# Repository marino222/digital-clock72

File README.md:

# Digital Kinetic Art Clock 

This project is the digital successor to my [ClockClock24 Project](https://github.com/marino222/clockclock24-replica), a replica of the kinetic art piece by [Humans Since 1982](https://www.humanssince1982.com/en-int). The original features physical clock hands driven by stepper motors, which brings challenges around power supply and makes scaling difficult.

This version replaces the clock hands with round LCD displays, which opens up new possibilities beyond just showing the time: animations, a snake game across all displays, or custom widgets.

---

## Table of contents

- [Vision](#vision)
- [Key decisions](#key-decisions)
- [How it works](#how-it-works)
- [Repository layout & component status](#repository-layout--component-status)
- [Roadmap](#roadmap)
- [Open questions](#open-questions)

---

## 🌅 Vision

The goal is to build a wall mounted array of round LCD displays that act together as one big synchronized screen. Each display sits in its own spot in a grid, similar to the clocks in the predecessor, but instead of physical hands every spot now has its own small screen.

At first, the array will simply show the time. But since every spot is now a real screen and not just a pair of clock hands, I plan to add more features over time. This includes smooth animations where the hands ease in and out instead of jumping, geometric patterns that move across the whole grid, a snake game that can be played across all displays at once, and small widgets like weather or notifications.

One central computer (likely a Raspberry Pi) will control the whole array and decide what should be shown. It sends this information to every display, and each display takes care of showing its own part of the picture.

---

## 🧩 Concept 

| Aspect | Choice | Why |
|---|---|---|
| Architecture | Master for calulation / Slave for rendering | Real time pixel drawing and global logic need different hardware |
| Master | Raspberry Pi 3, headless Linux broadcasts state at 60 Hz | Global logic and the web UI run better on a Pi than on a microcontroller |
| Node (Slave) | 1× bare RP2040 + 1× GC9A01 round LCD, on a small custom PCB | One identical board, JLCPCB assembled, just replicated |
| Bus | RS485, daisy chained node to node | Carries tiny state packets instead of full frames, so it scales cleanly |
| Applications | Time, animated patterns, array wide games (Snake) | All just different states broadcast by the master |

---

## ⚙️ How it works

To make the vision above work, the project splits the thinking and the drawing onto different controllers. One controller calculates the global image/animation and broadcasts these to the nodes. Each node controller then renders its individual pixels and displays them.

```
        ┌───────────────────────────────────────────────┐
        │  MASTER (Raspberry Pi 3)                      │
        │  • Headless Linux, C#                         │
        │  • Time sync, global vector math, game logic  │
        │  • Web UI for control/config                  │ 
        └───────────────────────┬───────────────────────┘
                                │  RS485 bus (broadcast)
                                │  tiny state packets @ 60 FPS
        ┌───────────┬───────────┼───────────┬───────────┐
        ▼           ▼           ▼           ▼           ▼
     ┌──────┐    ┌──────┐    ┌──────┐    ┌──────┐    ┌──────┐
     │ NODE │    │ NODE │    │ NODE │    │ NODE │    │ NODE │  
     │RP2040│    │  +   │    │  +   │    │  +   │    │  +   │
     │GC9A01│    │ LCD  │    │ LCD  │    │ LCD  │    │ LCD  │
     └──────┘    └──────┘    └──────┘    └──────┘    └──────┘
   Each node renders its own pixels locally from the shared global state.
```

### The master and the slave nodes

One computer, the master controller, runs the whole logic. It keeps track of time, decides what the array should be displaying, and runs a simple web page so it can be controlled. Every screen has its own slave controller, together they make up a node. Each node holds the picture for its own screen and draws it fast enough to keep up with all the others. It also knows its own position in the grid, so it only draws its own little piece of the bigger picture. The work is split this way because one controller can think for the whole array, but it cannot draw fast enough on dozens of screens by itself. And a tiny slave controller is fast enough to draw one screen, but it is too small to run all the planning logic. Splitting the work lets both sides do what they are good at. There is also a hard numeric reason the nodes have to render locally. One screen is 240×240 pixels at 16-bit color (RGB565), so one full frame is 240 × 240 × 2 bytes ≈ **112.5 KiB**. The RP2040 on each node has 264 KiB of SRAM, so it comfortably fits a double buffer for its *own* screen (≈225 KiB) with room to spare.

Read more about the master controller in [`master/README.md`](master/README.md), about the nodes in [`slave/README.md`](slave/README.md), and about the
hardware behind them in [`pcb/README.md`](pcb/README.md).

### How the data is sent to the nodes

Here is the idea that makes the whole array possible. The master does not send a full picture to every screen, sixty times a second. That would be far too much data. Instead, it sends a tiny instruction, something like "the hand should now point at 45 degrees" or "the snake is now at position 12, 2." Every node controller receives the exact same tiny instruction at the exact same moment, and draws its own piece of the picture from it. Streaming one full frame to one screen at 60 FPS is 112.5 KiB × 60 ≈ **6.6 MB/s**, for a single screen alone. For 9 nodes that is already ≈ 60 MB/s, at the full 72-node array it is ≈ 475 MB/s. A wired RS485 bus, the kind of connection this project uses, realistically carries somewhere in the low single-digit Mbit/s over a long daisy chain, several hundred times too little. A state instruction, on the other hand, is a handful of bytes sent once, at 60 Hz, no matter how many screens are listening. That gap is the entire reason the master only ever sends instructions, never pixels. This has three nice side effects. It needs very little data, since an instruction is just a handful of bytes instead of a full image. It keeps everything in sync automatically, since every screen hears the same instruction at the same time. And it scales easily, since adding more screens does not change how much data the brain has to send.

To reliably send state instruction a Data Protocol needs to be defined. Read more about this in [`master/README.md`](master/README.md) and [`slave/README.md`](slave/README.md).

### What actually will be displayed

This instruction can describe anything, which is what makes the project exciting. So far the plan includes:

- **Time:** the original purpose, digits and clock faces drawn across the grid.
- **Geometric and animated patterns:** motion across the whole grid, with easing animations instead of sudden jumps.
- **A snake game:** one game played across the entire array at once.
- **Small widgets:** controlled from the brain's simple web page.
- **Gifs**

---

## 📦 Repository layout & component status

```
Digital Clock 72/
├── 3D files/
│   ├── final/
│   └── test/
├── docs/
│   ├── datasheets/
│   └── images/
├── master/
│   └── README.md
├── slave/
│   └── README.md
├── pcb/
│   ├── node-pcb/
│   └── README.md
├── power/
│   └── README.md
├── tests/
│   ├── phase-1.1-display-performance/
│   └── README.md
└── README.md
```

| Path | Tech | Role | Status |
|---|---|---|---|
| **master/** | C# on Pi 3 | Global logic, time sync, vector math, games, web UI, RS485 broadcast | Conceptual |
| **slave/** | C++ (PlatformIO), RP2040 | Framebuffer + SPI/DMA rendering, RS485 receive, local draw, auto-addressing | Conceptual |
| **node_pcb/** | KiCad | Single-node board (RP2040 + GC9A01 display header + RS485 + power + USB-C/SWD) | In design |
| **power/** | — | Power supply and wiring for all 72 nodes, based on measured values | In design |
| **tests/** | — | Bring-up plan test procedures and recorded results, one folder per phase | Not started |

---

## 🗺️ Roadmap

This roadmap tracks the project progress. The approach is to test cheap, risky parts first before committing to PCB production. The prototype is a **2×2 (4-node)** array, large enough to validate the bus, addressing, and power distribution without high cost. Notes for each phase are listed in [`tests/`](tests/).

| Phase | Goal | Status |
|---|---|---|
| 1 | Test a single display at 60 FPS and measure power | ✅ Completed|
| 2 | Prove the RS485 link with a disposable test sender | ✅ Completed |
| 3 | Prove the state protocol and slave firmware on breadboards | ✅ Completed|
| 4 | Confirm the display hardware | ⚙ In progress |
| 5 | Build small prototype | ⚙ Not started |
| 6 | Scale to 24, then 72 nodes | ⬜ Not started |
| 7 | Add applications and the web UI | ⬜ Not started |

<details>
<summary><strong>1. Test a single display at 60 FPS and measure power</strong></summary>

**1.1 Display performance (breadboard)**
- One GC9A01 dev board driven by a Pico
- Aim for 60 FPS

**1.2 Power measurement (run during 1a)**
- Measure how much power a single display and Pico consume

</details>

<details>
<summary><strong>2. Prove the RS485 link with a disposable test sender</strong></summary>

A slave can't be tested without something transmitting packets, so a sender has to exist this early, but it doesn't need to be the real master. A minimal, throwaway sender (a second Pico, or even a PC-side script) is enough to put bytes on the bus.

**2.1 RS485 link (breadboard)**
- Two Picos + two cheap RS485 breakout modules (MAX3485 / THVD1450).
- One Pico runs a minimal, disposable packet sender the other renders them as a slave.
- The packet should contain very basic instructions so the slave can draw something

</details>

<details>
<summary><strong>3. Prove the state protocol and slave firmware on breadboards</strong></summary>

Develop and test the state protocol and rendering pipeline on breadboards before committing to custom PCBs. Use a Pico as a sender.

**3.1 Protocol design**
- Define and implement the state protocol: time display, basic drawing instructions, interface to implement widgets later
- Build the slave display-list executor: the firmware loop that parses commands, calls into a graphics library (TFT_eSPI or LovyanGFX) and displays pictures

**3.2 Physical testing**
- Test sync accross multiple nodes on 2–3 Picos: one sender, two slaves rendering the same broadcast
- Addressing here is manual, daisy-chain auto-addressing comes later

</details>

<details>
<summary><strong>4. Confirm the display hardware</strong></summary>

**4.1 Display hardware samples**
- Order a handful of the chosen GC9A01 breakout displays before finalizing any PCB.
- Confirm the breakout's pinout/pin order and its mounting-hole pattern / board outline, so the node board's mating board-to-board header position and any standoffs line up

</details>

<details>
<summary><strong>5. Build small prototype</strong></summary>

Before any further testing we should design the PCB as best as we can. Since the minimum order on JLCPCB is 5 pieces, 4 of them should be used to build a 2x2 prototype.

**5.1 PCB Prototype design**
- Design PCB
- Order a small batch (5 Pcs.) and bring up one board: power rails, USB enumeration, flashing, display, RS485 loopback.
- Test if the board works fine: Try to send data packets via RS485 using the sender from Phase 1b
- Measure the power consumption of this board

**5.2 2x2 prototype**
- Add daisy-chain auto-addressing in firmware, now that multiple nodes make it meaningful.
- Create a first version of the master controller in C#
- Assemble prototype and run tests
- Watch for voltage drops along the chain and try the mid-chain injection point to see how much it helps.

</details>

<details>
<summary><strong>6. Scale to 24, then 72 nodes</strong></summary>

**6.1 Scale**
- With real power numbers and a working board/bus, scale up.
- Power distribution will probably need its own pass at this size (multiple supplies, injection points, trace/connector currents).
- Adjust PCB design if anything arises

</details>

<details>
<summary><strong>7. Add applications and the web UI</strong></summary>

**7.1 Applications & web UI**
- Patterns, Snake, widgets. Once the transport feels solid, this part is mostly open-ended.

</details>

---

## ❓ Open questions

- **Power at scale.** Per-node draw and voltage drop are measured, see [power/](power/README.md). Still open: inrush current, fusing, master power.
- **Broadcast protocol definition.** Exact protocol definition. Needs to be implemented in `master` and `slave`.
- **Addressing scheme (firmware).** Daisy-chain auto-addressing to be *implemented* in firmware.
- **Syncing** How to make sure all displays run in sync

---

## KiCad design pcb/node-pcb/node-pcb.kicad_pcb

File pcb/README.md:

# Node PCB

Each pixel node is one self contained board carrying one microcontroller and one round LCD, wired to its neighbors over a shared bus. The full array is this same board built N times, with a target of 72 nodes. This README describes one of the nodes.

## What the board contains

- An RP2040 microcontroller and an external flash chip
- A connector for the GC9A01 round LCD
- An RS485 transceiver and two bus connectors so boards can be daisy chained
- Power regulation, with separate rails for the logic and the display backlight
- USB-C and/or SWD pads for flashing firmware

## Design reference

The board layout follows Raspberry Pi's RP2040 [hardware design guidelines](/docs/datasheets/hardware-design-with-rp2040.pdf), which include a minimal RP2040 example design. Its KiCad files are open source, so they are used as the starting reference.

The image above shows this minimal design. Core components like the crystal oscillator, flash chip, and voltage regulator should stay the same. From there:

- Remove unnecessary I/O pins
- Add a 12-pin ZIF connector for the display
- Add the components needed for RS485 communication
- Add connectors for the power supply (power is not longer supplied via USB)
- Replace the Bootsel jumper pins (J2) with a button

Only SMD components are used, so the boards can be assembled by machine.

## Block diagram 

## List of components

> All components need to be available in the JLCPCB parts library so they can be used for automatic assembly. Should they not be available, a suitable alternative has to be found.

Common parts like resistors and capacitors are not shown in this list. They may be viewed on the BOM of the final PCB design.

| Part | Manufacturer number | JLCPCB part number |  used in reference design |
| --- | --- | --- | --- | 
| MCU | RP2040 | C2040 | ✅ |
| Flash, 4 MB | W25Q32JVS | C97521 | ✅ |
| Crystal, 12 MHz | ABM8-272-T3 | C20625731 | ✅ |
| USB-C connector | TYPE-C-31-M-12 | C165948 | ❌ |
| BOOTSEL button | TS-1187A-B-A-B | C318884 | ❌ |
| RS485 transceiver | THVD1450DR | C2671361  | ❌ |
| ZIF, vertical | AFC11-S12ICA-00 | C262499 | ❌ |
| Schottky diode | B5819W SL | C8598 | ❌ |
| JST connector, 8-pin | BM08B-GHS-TBT(LF)(SN) | C133062 | ❌ |
| LDO voltage regulator | AP2112K-3.3TRG1 | C51118 | ❌ |

> Note that the listed flash chip isn't the same as in the reference design. There a 16 Mb chip is used, which is very likely overkill for this project. To save costs this is scaled down to a 4 Mb chip. For this purpose the [hardware design guidelines](/docs/datasheets/hardware-design-with-rp2040.pdf) explicitly states that most 25-series flash devices may be used. So by using a smaller capacity storage from the same manufacturer shouldn't cause any trouble.

---
---
# Designing the PCB

As a starting point, the KiCad files of the minimal example mentioned above we're copied. 

## Adjusting schematic

The first step is to adjust the [schematic](/docs/datasheets/rp2040-design-example-schematic.pdf) to our needs.

### Power supply

<table>
    <tr>
        <td><b>Before</b></td>
        <td><b>After</b></td>
    <tr>
        <td></td>
        <td></td>
    </tr>
</table>

The image on the left shows the power block of the minimal example, the image on the right shows our version. What changed:

- The Micro USB connector is replaced by a USB-C connector (J1). Its shield pins are tied directly to ground. The two D+ pins (A6/B6) are tied together, and so are the two D- pins (A7/B7), so the port works in either plug orientation. Both pairs then run to the MCU through 33 Ω series resistors.
- CC1 and CC2 are each pulled down with a 5.1 kΩ resistor. This is what tells the host that our board is a sink, so it enables +5 V on VBUS.
- To supply a steady 3.3V, the AP2112K-3.3TRG1 voltage regulater was chosen. This differs from the reference design, mainly because it has a lower dropout voltage (see below)

**Two power sources, two diodes**

During normal operation the board is not powered over USB, that port is only for development and testing. Power comes in over a JST connector, which also carries the RS485 signal lines. Each node has two of these connectors, so a board can be passed through to the next one in a daisy chain.

That means both sources can be present at the same time, so two Schottky diodes keep them apart:

- **D1** sits between the bus (JST) +5 V net and the board's internal +5 V node (`5V_LOCAL`). It lets the bus feed the board, but stops the USB port from feeding the other boards on the bus.
- **D2** sits between the USB-C VBUS pin and that same internal node. It lets the USB port feed the board, but blocks current from flowing back into the USB connector.

If both sources are active, the board is simply supplied from the one with the higher potential. The price for this protection is a voltage drop across the diode, which is what the rest of this section is about.

#### How much input voltage does one board need?

Figure 1 shows a simplified version of our power supply circuit. The standard case is that the board is supplied over the bus, so the path is JST → D1 → LDO.

<table>
    <tr>
        <td></td>
        <td></td>
    </tr>
    <tr>
        <td><b>Figure 1:</b> Simplified power path of one node. Both inputs reach the LDO through their own Schottky diode, so whichever drives the input, one diode drop is always in the way.</td>
        <td><b>Figure 2:</b> Forward characteristics of the B5819W. At I_F = 100 mA (red dot) the forward voltage is roughly 0.3 V.</td>
    </tr>
</table>

Measured on the prototype ([tests](/tests/README.md), section L), one board draws at most 84 mA. The calculation below uses **100 mA per board** as a round upper bound.

Two parts in that path define the minimum input voltage, both taken at 100 mA:

| Part | Value at 100 mA | Source |
| --- | --- | --- |
| Schottky diode (B5819W) | V_F ≈ 0.3 V | [datasheet](/docs/datasheets/schottky-diode-B5817W-589W.pdf), see Figure 2 |
| AP2112K LDO | V_in - V_out ≈ 45 mV | [datasheet](/docs/datasheets/AP2112-LDO.pdf), see Performance Characteristics |

The 45 mV is the LDO's *dropout voltage*: the **minimum** difference the regulator needs between its input and its output. If V_in - V_out falls below it, the LDO drops out of regulation and the 3.3 V rail starts to sag. With V_out = 3.3 V that gives:

```
V_in(LDO) >= V_out + V_dropout = 3.3 V + 0.045 V = 3.345 V
V_bus     >= V_in(LDO) + V_F   = 3.345 V + 0.3 V = 3.645 V
```

So the +5 V on the bus connector must never drop below **≈3.7 V**, anywhere in the installation.

#### How much is left at the last board?

How the boards are chained, how much voltage is left at the last board of a row, and how to size the PSU is described in the [power supply README](/power/README.md). In short: with the measured values, the last board of a row still gets more than 4.5 V, well above the 3.7 V minimum.

### Flash storage

<table>
    <tr>
        <td><b>Before</b></td>
        <td><b>After</b></td>
    </tr>
    <tr>
        <td></td>
        <td></td>
    </tr>
</table>

The only changes here are replacing the BOOTSEL jumper J2 with a button (SW1) for easier entry into bootselect mode, and swapping in a different flash chip that shares the exact same footprint as the one in the reference design.

### RS485 communication

**Why this transceiver.** The THVD1450DR is a 1/8 unit-load part, so up to 256 nodes can share one bus segment. Since the array targets 72 nodes, that leaves plenty of headroom. It is also a common, widely available part and is stocked by JLCPCB.

**What the circuit does.** U4 runs off +3V3 and connects the RP2040's UART to the differential pair:

- `GPIO12_TX` → `DI` and `RO` → `GPIO13_RX` carry the data.
- `GPIO14_DE` and `GPIO15_RE` control the direction. Both are pulled to GND through 10 kΩ (R6, R9), so on power-up the driver is disabled and the receiver is enabled.
- C18 (100 nF) sits directly at pin 8, with C19 (1 µF) immediately upstream on the same 3V3 feed.

This follows the layout guidelines in the chip's [datasheet](/docs/datasheets/thvd1450.pdf), which ask for a 100–220 nF cap as close as possible to VCC, at least two vias per decoupling connection, and 1–10 kΩ resistors on the enable lines to limit noise currents during transients. 

**Termination.** R12 (120 Ω) is populated on every board but sits in series with solder jumper JP1, so it is only in circuit once that jumper is bridged. That matters because of how the array is wired. Looking back at the [wiring diagram](/docs/images/wiring-diagram.png), this is not one continuous bus. The 72 nodes are split into 12 rows of 6, each fed from its own injection point, so electrically there are 12 separate branches. Each branch is a short run, and terminating all 24 ends is likely overkill. How many jumpers actually need bridging still has to be measured on real hardware.

### Daisy chain connector

Boards are linked with 8-pin JST GH connectors (BM08B-GHS-TBT), one in (J3) and one out (J2). 

The eight lines are allocated as follows:

| Pins | Net | Notes |
| --- | --- | --- |
| 1, 4 | GND | Split across two pins |
| 2, 3 | +5V (VBUS) | Split across two pins |
| 5, 6 | RS485_A / RS485_B | Passed straight through |
| 7 | ADDR | Point to point, for auto-addressing |
| 8 | SPARE | Point to point, reserved |

Power and ground each get two pins on purpose. The GH series is rated for 1.0 A per contact with AWG #26 wire, so doubling up gives a comfortable 2 A budget.

The last two lines are wired differently from the rest. Power, ground and the RS485 pair passed straight through the board, `ADDR` and `SPARE` are not. `ADDR_IN`/`SPARE_IN` on J3 and `ADDR_OUT`/`SPARE_OUT` on J2 are four separate nets going to four separate GPIOs. `ADDR` is used for the auto adressing feature. `SPARE` is the same arrangement with nothing assigned to it yet, wired up proactively so a future feature can use it without a board change. `ADDR` and `SPARE` are directly wired to the MCU's GPIO pins, which could in theory be damaged by too large current delivery. Therefore, four 1 kΩ resistors are wired in series.

C20 (10 µF) provides local bulk decoupling between +5V and GND at the connector.
### SWD Debug

An SWD header (J4) was added alongside USB-C to make flashing and debugging easier. The footprint is from a 2.54 mm header pin. Spring loaded pogo pins with the same pitch can be inserted into the through holes.

On the other end, the plan is to drive it from a second Raspberry Pi Pico running the official debugprobe firmware, which handles both flashing and interactive debugging over the same three wires.

### SPI display

The display's flex cable plugs into J5, a 12-pin ZIF connector, so the panel can be swapped without soldering. The pinout follows the panel [datasheet](/docs/datasheets/HZ0128QVPHGWS01N-AA).

| Pin | Net | Purpose |
| --- | --- | --- |
| 1 | GND | |
| 2 | LEDK | Backlight cathode, switched by Q1 |
| 3 | LEDA | Backlight anode, +5V through R11 |
| 4 | +3V3 | VDD, analog supply |
| 5, 6 | GND | |
| 7 | D/C | Data / command select |
| 8 | CS | Chip select, active low |
| 9 | SPI0_SCK | Serial clock |
| 10 | SPI0_TX | Serial data in |
| 11 | RESET | Active low |
| 12 | GND | |
| 13, 14 | GND | Mounting tabs |

Most pins are straightforward: SPI signals, `RESET`, power and ground. VDD runs from +3V3 (2.8 V typical, 4.6 V max). Only the backlight uses +5V.

**Backlight.** The panel has two white LEDs in parallel (VF ≈ 3.0 V, IF = 40 mA) and no driver of its own.

- **Anode (`LEDA`)** is fed from +5V, since 3.3 V leaves too little headroom above the 3.0 V forward voltage.
- **Cathode (`LEDK`)** is switched to ground by Q1, an S8050 NPN transistor.
- **`BL_PWM`** drives Q1's base through R13 (2.2 kΩ). PWM duty cycle sets the brightness.
- **R14** (10 kΩ) pulls the base low, so the backlight stays off until the firmware turns it on.

R11 (47 Ω) in series with the anode sets the current:

```
I = (5 V − 3.0 V − 0.2 V) / 47 Ω ≈ 38 mA
```

The 0.2 V is Q1's saturation voltage. The result sits just under the 40 mA rating.

**Measured** ([tests](/tests/README.md), sections H and M): 39 mA at 5.09 V. Since nothing regulates the current, it follows the supply: about 2 mA less for every 0.1 V less, 31 mA at 4.75 V on the bus. At 5.25 V it would be about 42 mA, above the rating. Two options for the next revision:
- R11 = 56 Ω keeps the LEDs below 40 mA up to 5.25 V.
- A constant-current LED driver would also make the brightness independent of the supply voltage.

What this means for the whole clock is described in the [power supply README](/power/README.md#brightness).

## PCB Layout

The board follows the outline, which was defined in the [mechanical design](/mechanical/README.md#pcb-outline). The display panel is mounted to the back of the board, and the boards are fully assembled by JLCPCB.

<table>
    <tr>
        <td align="center" width="50%"></td>
        <td align="center" width="50%"></td>
    </tr>
    <tr>
        <td align="center"><sub>Top</sub></td>
        <td align="center"><sub>Bottom</sub></td>
    </tr>
</table>

### Layer stackup

A 4-layer board was chosen over a 2-layer one. The RP2040 needs a lot of short, clean decoupling and ground connections, and squeezing that plus the QSPI flash bus, USB and the display SPI onto two layers would mean compromises everywhere. The stackup is JLCPCB's standard  1.6 mm 4-layer build [JLC04161H-7628 Stackup](https://jlcpcb.com/impedance).

| Layer | Name | Copper weight | Use |
| --- | --- | --- | --- |
| 1 | `Toplayer` | 1 oz | Signal, all components, almost all routing |
| 2 | `GND` | 0.5 oz | Solid **GND** plane |
| 3 | `+3V3` | 0.5 oz | Power plane: **+3V3** pour, with zones for `+5V_BUS` and `VBUS_USB-C` |
| 4 | `Bottomlayer` | 1 oz | Additional signal lines|

### Component Placement

Placement follows the blocks from the [schematic](/pcb/schematic.pdf). The image below tries to classify each area of the pcb.

### Routing

Multiple net classes are used to define track widths and clearances. A custom ruleset for DRC was used (see below).

These two main design principles were followed:

**Critical nets stay on one layer.** The QSPI flash bus, the crystal lines and the display SPI signals are routed entirely on `F.Cu` with no vias at all, so the ground plane underneath them is never interrupted.

**The bottom layer stays almost empty.** The bottom is used only for short crossovers that could not be solved on top. Everything else is left to the two inner planes, and about half of all vias on the board are ground stitching vias tying the top copper down to the GND plane.

<table>
    <tr>
        <td align="center" width="50%"></td>
        <td align="center" width="50%"></td>
    </tr>
    <tr>
        <td align="center"><sub><b>Top side:</b> all components and nearly all routing</sub></td>
        <td align="center"><sub><b>Bottom layer:</b> only a few short crossovers, the rest is left to the planes</sub></td>
    </tr>
</table>

## Design Verification

**Schematic review with AI.** The schematic was run through [traceformer.io](https://traceformer.io), an AI based design review tool, to look for electrical mistakes.

**DRC inside KiCad.** KiCad's own defaults say nothing about what the fab can actually build, so the board is checked against [`node-pcb.kicad_dru`](node-pcb/node-pcb.kicad_dru). That file is a ruleset generated from JLCPCB's published [capabilities](https://jlcpcb.com/capabilities/pcb-capabilities), taken from [kicad-druid](https://github.com/Cimos/kicad-druid) in the `4L-1oz` variant matching this order (4 layer, 1 oz outer / 0.5 oz inner).

**JLCPCB DFM analysis** The exported gerbers were additionally run through JLCPCB's DFM analysis tool. It reviews the actual production files against their process and catches what a rules file cannot, such as silkscreen over pads or solder mask slivers.

## Manufacturing

The boards are made and assembled by JLCPCB. Everything needed for an order is in [`node-pcb/jlcpcb/production_files/`](node-pcb/jlcpcb/production_files/):

| File | Upload as |
| --- | --- |
| `GERBER-node-pcb.zip` | Gerber files |
| `BOM-node-pcb.csv` | Bill of materials |
| `CPL-node-pcb.csv` | Pick and place file |

Order settings that differ from the defaults:

- **Layers:** 4
- **Stackup:** JLC04161H-7628 (see [Layer stackup](#layer-stackup))
- **PCB assembly:** yes, top side

## Open uncertainties

- Inrush current at power-up hasn't been measured yet.
- How many of the 12 branches actually need their 120 Ω termination jumper bridged has to be measured.
- Baud rate vs. max bus length for the largest planned install needs to be decided.

See the root [README.md](../README.md) for full system context.

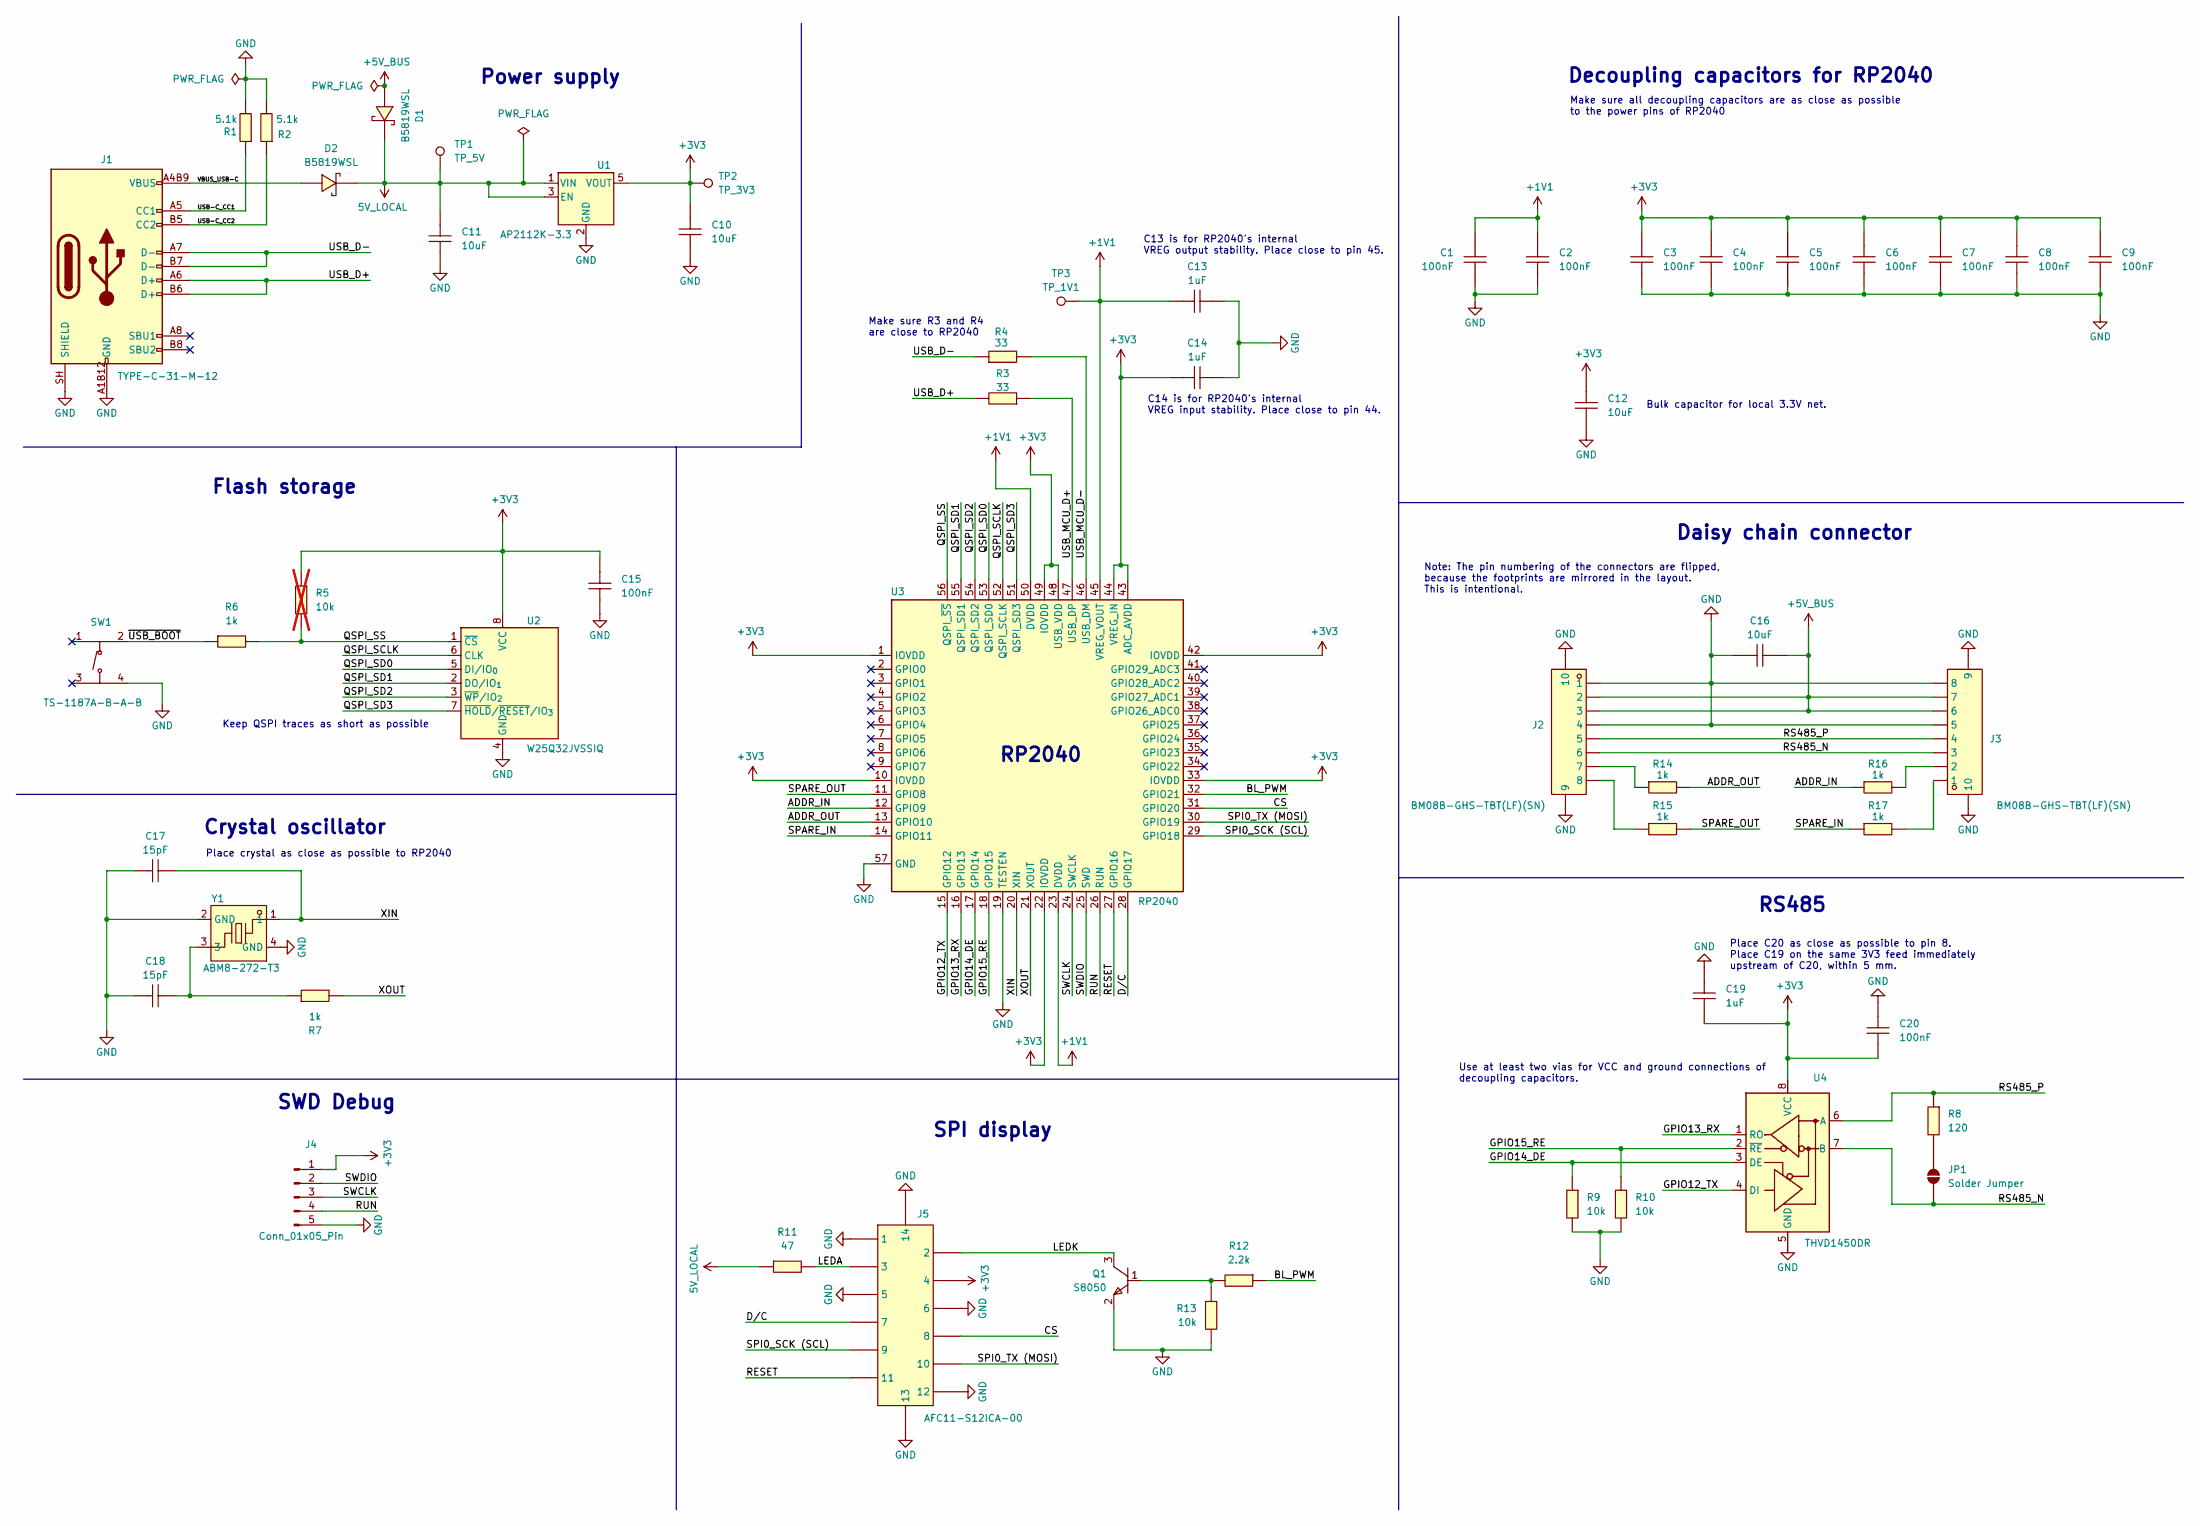
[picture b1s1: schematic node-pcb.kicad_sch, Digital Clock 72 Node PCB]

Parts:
C1, C2, C3, C4, C5, C6, C7, C8, C9, C15, C20: 100nF; C0402; tolerance ± 10%; voltage 16V; MPN CL05B104KO5NNNC; LCSC Part C1525
C10: 10uF; C0805; tolerance ± 10%; voltage 25 V; MPN CL21A106KAYNNNE; LCSC Part C15850
C11, C12, C16: 10uF; C0805; tolerance ± 10%; voltage 25 V; MPN GRM21BR61C106KE15L; LCSC Part C15850
C13, C14, C19: 1uF; C0402; tolerance ± 10%; voltage 25V; MPN CL05A105KA5NQNC; LCSC Part C52923
C17, C18: 15pF; C0402; tolerance ± 5%; voltage 50V; MPN 0402CG150J500NT; LCSC Part C1548
D1, D2: B5819WSL; SOD-123_L2.7-W1.6-LS3.7-RD-1; MPN B5819W SL; LCSC Part C8598
J1: TYPE-C-31-M-12; USB-C_SMD-TYPE-C-31-M-12_1; LCSC Part C165948
J2, J3: BM08B-GHS-TBT(LF)(SN); CONN-SMD_BM08B-GHS-TBT-LF-SN; MPN BM08B-GHS-TBT(LF)(SN); LCSC Part C133062
J4: Conn_01x05_Pin; PinSocket_1x05_P1.27mm_Vertical
J5: AFC11-S12ICA-00; CONN-SMD-12P_AFC11-S12ICA-00; MPN AFC11-S12ICA-00; LCSC Part C262499
JP1: Solder Jumper; SolderJumper-2_P1.3mm_Open_RoundedPad1.0x1.5mm
Q1: S8050; SOT-23-3_L3.0-W1.7-P0.95-LS2.9-BR; MPN S8050 J3Y(RANGE:200-350); LCSC Part C2146
R1, R2: 5.1k; R0603; tolerance ± 1%; voltage 75V; MPN 0603WAF5101T5E; LCSC Part C23186
R3, R4: 33; R0402; tolerance ± 1%; voltage 50V; MPN 0402WGF330JTCE; LCSC Part C25105
R5: 10k; R0402; MPN 0402WGF1002TCE; LCSC Part C25744; not fitted
R6, R7, R14, R15, R16, R17: 1k; R0402; tolerance ± 1%; voltage 50V; MPN 0402WGF1001TCE; LCSC Part C11702
R8: 120; R0402; tolerance ± 1%; voltage 50V; MPN 0402WGF1200TCE; LCSC Part C25079
R9, R10, R13: 10k; R0402; tolerance ± 1%; voltage 50V; MPN 0402WGF1002TCE; LCSC Part C25744
R11: 47; R0805; tolerance ± 1%; voltage 150V; MPN 0805W8F470JT5E; LCSC Part C17714
R12: 2.2k; R0402; tolerance ± 1%; voltage 50V; MPN 0402WGF2201TCE; LCSC Part C25879
SW1: TS-1187A-B-A-B; SW-SMD_4P-L5.1-W5.1-P3.70-LS6.5-TL_H1.5; MPN TS-1187A-B-A-B; LCSC Part C318884
TP1: TP_5V; TestPoint_Pad_D1.0mm
TP2: TP_3V3; TestPoint_Pad_D1.0mm
TP3: TP_1V1; TestPoint_Pad_D1.0mm
U1: AP2112K-3.3; SOT-25-5_L2.9-W1.6-P0.95-LS2.8-BL; MPN AP2112K-3.3TRG1; LCSC Part C51118
U2: W25Q32JVSSIQ; SOIC-8_L5.3-W5.3-P1.27-LS8.0-BL; manufacturer_pn W25Q32JVSSIQ; LCSC Part C179173
U3: RP2040; LQFN-56_L7.0-W7.0-P0.4-EP; manufacturer_pn RP2040; LCSC Part C2040
U4: THVD1450DR; SOIC-8_L4.9-W3.9-P1.27-LS6.0-BL; manufacturer_pn THVD1450DR; LCSC Part C2671361
Y1: ABM8-272-T3; CRYSTAL-SMD_4P-L3.2-W2.5-BL; manufacturer_pn ABM8-272-T3; LCSC Part C20625731

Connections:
5V_LOCAL: C11.1, D1.1 (-), D2.1 (-), R11.1, TP1.1 (1_1), U1.1 (VIN), U1.3 (EN)
+1V1: C1.1, C2.1, C13.2, TP3.1 (1_1), U3.23 (DVDD), U3.45 (VREG_VOUT), U3.50 (DVDD)
+3V3: C3.1, C4.1, C5.1, C6.1, C7.1, C8.1, C9.1, C10.1, C12.1, C14.1, C15.1, C19.2, C20.2, J4.1, J5.4, R5.1, TP2.1 (1_1), U1.5 (VOUT), U2.8 (VCC), U3.1 (IOVDD), U3.10 (IOVDD), U3.22 (IOVDD), U3.33 (IOVDD), U3.42 (IOVDD), U3.43 (ADC_AVDD), U3.44 (VREG_IN), U3.48 (USB_VDD), U3.49 (IOVDD), U4.8 (VCC)
+5V_BUS: C16.2, D1.2 (+), J2.2, J2.3, J3.6, J3.7
/ADDR_IN: R16.1, U3.12 (GPIO9)
/ADDR_OUT: R14.2, U3.13 (GPIO10)
/BL_PWM: R12.1, U3.32 (GPIO21)
/CS: J5.8, U3.31 (GPIO20)
/D/C: J5.7, U3.28 (GPIO17)
/GPIO12_TX: U3.15 (GPIO12), U4.4 (DI)
/GPIO13_RX: U3.16 (GPIO13), U4.1 (RO)
/GPIO14_DE: R9.1, U3.17 (GPIO14), U4.3 (DE)
/GPIO15_RE: R10.1, U3.18 (GPIO15), U4.2 (~RE)
/LEDA: J5.3, R11.2
/LEDK: J5.2, Q1.3 (C)
/QSPI_SCLK: U2.6 (CLK), U3.52 (QSPI_SCLK)
/QSPI_SD0: U2.5 (DI/IO_{0}), U3.53 (QSPI_SD0)
/QSPI_SD1: U2.2 (DO/IO_{1}), U3.55 (QSPI_SD1)
/QSPI_SD2: U2.3 (~WP/IO_{2}), U3.54 (QSPI_SD2)
/QSPI_SD3: U2.7 (~HOLD/~RESET/IO_{3}), U3.51 (QSPI_SD3)
/QSPI_SS: R5.2, R6.2, U2.1 (~CS), U3.56 (QSPI_~SS)
/RESET: J5.11, U3.27 (GPIO16)
/RS485_N: J2.6, J3.3, JP1.2 (B), U4.7 (B)
/RS485_P: J2.5, J3.4, R8.1, U4.6 (A)
/RUN: J4.4, U3.26 (RUN)
/SPARE_IN: R17.1, U3.14 (GPIO11)
/SPARE_OUT: R15.2, U3.11 (GPIO8)
/SPI0_SCK (SCL): J5.9, U3.29 (GPIO18)
/SPI0_TX (MOSI): J5.10, U3.30 (GPIO19)
/SWCLK: J4.3, U3.24 (SWCLK)
/SWDIO: J4.2, U3.25 (SWD)
/USB-C_CC1: J1.A5 (CC1), R1.1
/USB-C_CC2: J1.B5 (CC2), R2.1
/USB_D+: J1.A6 (D+), J1.B6 (D+), R3.2
/USB_D-: J1.A7 (D-), J1.B7 (D-), R4.1
/USB_MCU_D+: R3.1, U3.47 (USB_DP)
/USB_MCU_D-: R4.2, U3.46 (USB_DM)
/VBUS_USB-C: D2.2 (+), J1.A4B9 (VBUS), J1.B4A9 (VBUS)
/XIN: C17.2, U3.20 (XIN), Y1.1
/XOUT: R7.2, U3.21 (XOUT)
/~USB_BOOT: R6.1, SW1.2 (B)
GND: C1.2, C2.2, C3.2, C4.2, C5.2, C6.2, C7.2, C8.2, C9.2, C10.2, C11.2, C12.2, C13.1, C14.2, C15.2, C16.1, C17.1, C18.1, C19.1, C20.1, J1.A1B12 (GND), J1.B1A12 (GND), J1.SH (SHIELD), J2.1, J2.4, J2.9, J2.10, J3.5, J3.8, J3.9, J3.10, J4.5, J5.1, J5.5, J5.6, J5.12, J5.13, J5.14, Q1.2 (E), R1.2, R2.2, R9.2, R10.2, R13.2, SW1.4 (D), U1.2 (GND), U2.4 (GND), U3.19 (TESTEN), U3.57 (GND), U4.5 (GND), Y1.2 (GND), Y1.4 (GND)
unnamed: C18.2, R7.1, Y1.3
unnamed: J2.7, R14.1
unnamed: J2.8, R15.1
unnamed: J3.1, R17.2
unnamed: J3.2, R16.2
unnamed: JP1.1 (A), R8.2
unnamed: Q1.1 (B), R12.2, R13.1

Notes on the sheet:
Power supply
Decoupling capacitors for RP2040
Crystal oscillator
C13 is for RP2040's internal VREG output stability. Place close to pin 45.
Bulk capacitor for local 3.3V net.
SWD Debug
Daisy chain connector
SPI display
Place crystal as close as possible to RP2040
RS485
C14 is for RP2040's internal VREG input stability. Place close to pin 44.
Place C20 as close as possible to pin 8. Place C19 on the same 3V3 feed immediately upstream of C20, within 5 mm.
Note: The pin numbering of the connectors are flipped, because the footprints are mirrored in the layout. This is intentional.
Keep QSPI traces as short as possible
Make sure R3 and R4 are close to RP2040
RP2040
Make sure all decoupling capacitors are as close as possible to the power pins of RP2040
Use at least two vias for VCC and ground connections of decoupling capacitors.
Flash storage

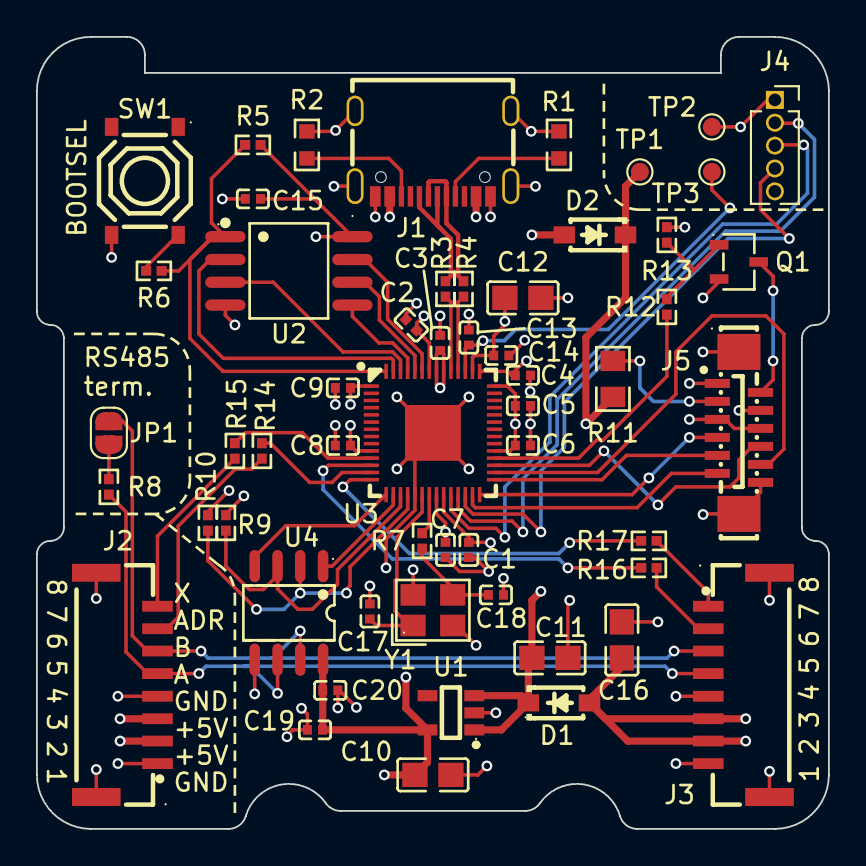
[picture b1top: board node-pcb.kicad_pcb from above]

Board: 4 copper layers, 44.0 x 44.0 mm, 55 parts (0 on the bottom side), 49 nets.

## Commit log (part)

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2026-06-17 Optimized readme
2026-06-20 Restructured READMEs for more clarity
2026-06-28 Simplified READMEs Added docs
